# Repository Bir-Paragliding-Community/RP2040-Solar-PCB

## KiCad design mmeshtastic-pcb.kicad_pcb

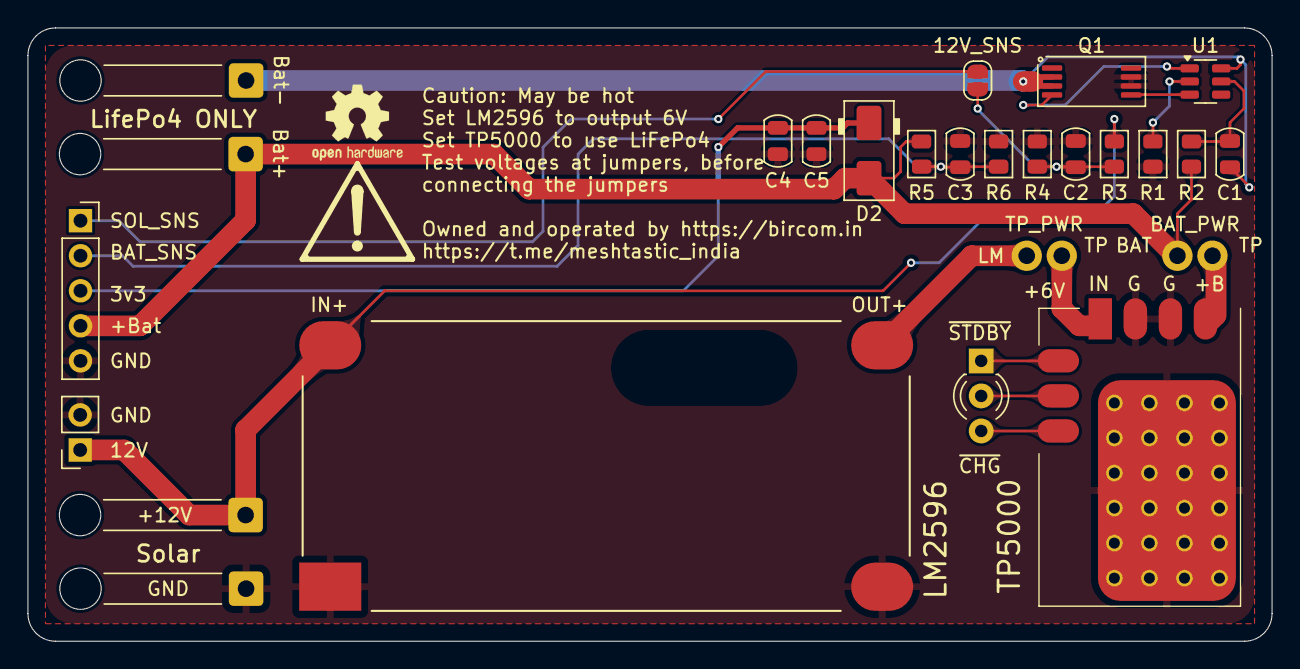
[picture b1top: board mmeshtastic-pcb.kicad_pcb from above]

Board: 2 copper layers, 90.2 x 44.5 mm, 29 parts (1 on the bottom side), 18 nets.

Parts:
C1, C2, C3, C4: 100nF; C_0805_2012Metric
C5: 10uF; C_0805_2012Metric
D1: LED_Dual_KAK; LED_D3.0mm-3
D2: SS16; D_SMA
J1: Conn_01x05; PinSocket_1x05_P2.54mm_Vertical
J2: Conn_01x02; PinSocket_1x02_P2.54mm_Vertical
JP1: TP_PWR; Jumper_P2.54mm_D1.2mm
JP2: BAT_PWR; Jumper_P2.54mm_D1.2mm
JP3: 12V_SNS; SolderJumper-2_P1.3mm_Open_RoundedPad1.0x1.5mm
M1: RP2040-LoRa-HF; LCC-32_L41.0-W21.0-P2.54-BL_RP2040-LoRa
Q1: FS8205A; TSSOP-8_4.4x3mm_P0.65mm
R1: 1K; R_0805_2012Metric
R2: 100; R_0805_2012Metric
R3: 150K; R_0805_2012Metric
R4: 20K; R_0805_2012Metric
R5: 10K; R_0805_2012Metric
R6: 100K; R_0805_2012Metric
SYM1: Logo_Open_Hardware_Small; OSHW-Logo2_7.3x6mm_SilkScreen
SYM2: Exclaimation; Symbol_Attention_Triangle_8x7mm_Copper
TP1, TP2, TP3, TP4: TestPoint; SolderWire-0.25sqmm_1x01_D0.65mm_OD2mm_Relief
U1: DW01A; SOT-23-6
U2: TP5000_Breakout_Akaddy
U3: LM2596 Module; module_LM2596

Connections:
+3V3: C4.2, C5.2, D2.1 (K), J1.3, M1.36 (3V3(OUT))
+6V: JP1.1 (A), U3.4 (OUT+)
+6V_TP: JP1.2 (B), U2.1 (IN+)
+12V: J2.1, R3.2, TP1.1, U3.1 (IN+)
+BATT: D2.2 (A), J1.4, JP2.2 (B), R2.1, R5.2, TP3.1
-BATT: C1.2, Q1.2, Q1.3, TP4.1, U1.6 (GND)
/BAT_SNS: C3.2, J1.2, M1.32 (GP27), R5.1, R6.2
/SOLAR_SNS: J1.1, JP3.2 (B), M1.31 (GP26)
GND: C2.1, C3.1, C4.1, C5.1, J1.5, J2.2, M1.3 (GND), M1.8 (GND), M1.13 (GND), M1.28 (GND), M1.33 (GND), M1.38 (GND), Q1.6, Q1.7, R1.2, R4.1, R6.1, TP2.1, U2.2 (GND), U2.4 (GND), U2.20 (GND), U3.2 (IN-), U3.3 (OUT-)
unnamed: D1.2 (A), U2.12 (LED_PWR)
unnamed: D1.1 (K1), U2.11 (~STDBY)
unnamed: D1.3 (K2), U2.10 (~CHRG)
unnamed: JP2.1 (A), U2.3 (OUT+)
unnamed: C2.2, JP3.1 (A), R3.1, R4.2
unnamed: R1.1, U1.2 (CS)
unnamed: Q1.5, U1.3 (OC)
unnamed: Q1.4, U1.1 (OD)
unnamed: C1.1, R2.2, U1.5 (VCC)

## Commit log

2024-09-16 Run DRC, everything checks out
